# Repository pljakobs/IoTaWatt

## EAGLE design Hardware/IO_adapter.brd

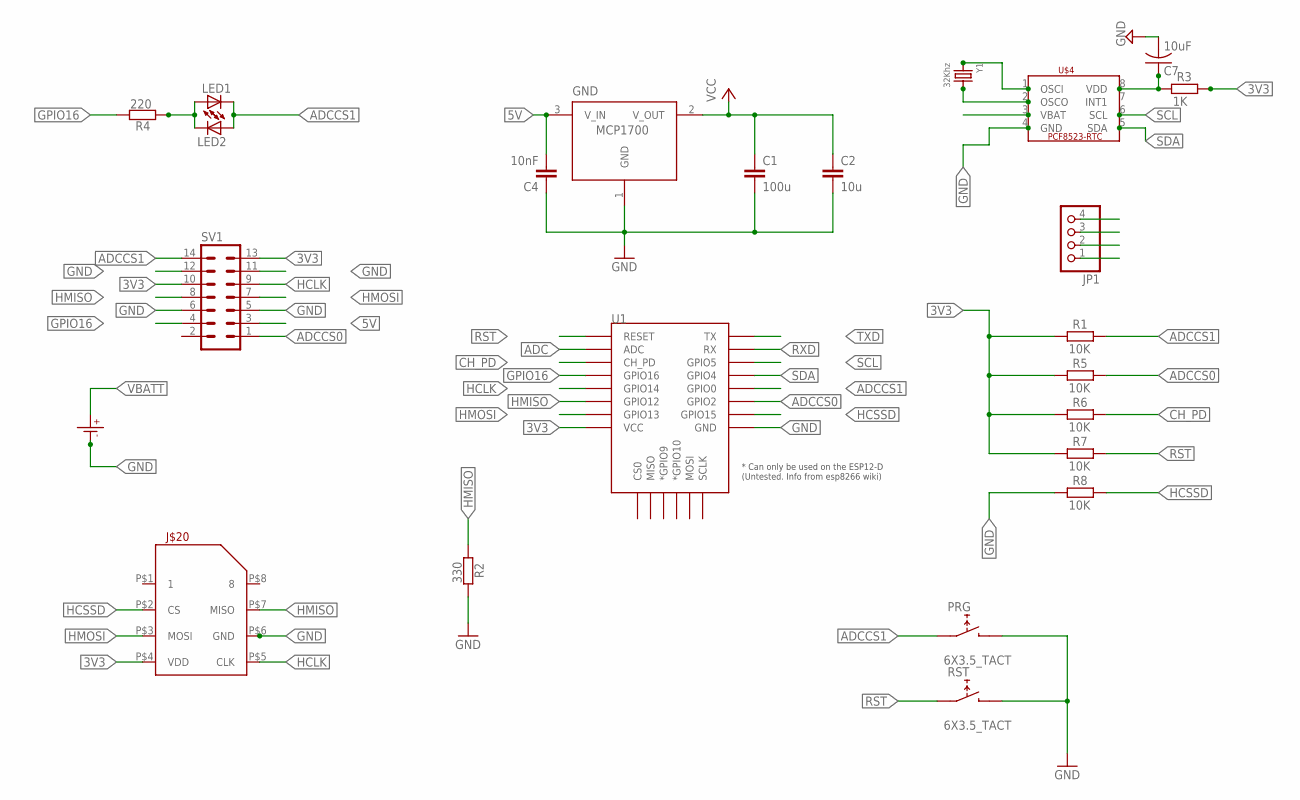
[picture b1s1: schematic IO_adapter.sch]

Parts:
C1: 100u; C0805
C2: 10u; C0805
C4: 10nF; C0805
C7: 10uF; C0805
GND: MCP1700SOT23; SOT-23
J$20: MICROSD_PUSH/PULL; MICROSD
JP1: PINHD-1X4; 1X04
LED1, LED2: LEDCHIPLED_0805; CHIPLED_0805
PRG: 6X3.5_TACT; TACT_6X3.5
R1, R5, R6, R7, R8: 10K; R0805
R2: 330; R0805
R3: 1K; R0805
R4: 220; R0805
RST: 6X3.5_TACT; TACT_6X3.5
SV1: MA07-2
U1: ESP12ESMD; ESP12E-SMD
U$1: CR1220SMD
U$4: PCF8523_RTC; SOIC_8
Y1: 32Khz; CRYSTAL_8X3.8

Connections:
3V3: C1.1, C2.1, GND.2 (V_OUT), J$20.P$4 (VDD), JP1.1, R1.1, R3.2, R5.1, R6.1, R7.1, SV1.10, SV1.13, U1.VCC
5V: C4.2, GND.3 (V_IN), SV1.3
ADC: U1.ADC
ADCCS0: R5.2, SV1.1, U1.GPIO2
ADCCS1: LED1.C, LED2.A, PRG.P$1 (1), R1.2, SV1.14, U1.GPIO0
CH_PD: R6.2, U1.CH_PD
GND: C1.2, C2.2, C4.1, C7.2, GND.1 (GND), J$20.P$6 (GND), JP1.4, PRG.P$2 (2), R2.2, R8.1, RST.P$2 (2), SV1.5, SV1.6, SV1.11, SV1.12, U1.GND, U$1.P- (P$-), U$4.4 (GND)
GPIO16: R4.2, SV1.4, U1.GPIO16
HCLK: J$20.P$5 (CLK), SV1.9, U1.GPIO14
HCSSD: J$20.P$2 (CS), R8.2, U1.GPIO15
HMISO: J$20.P$7 (MISO), R2.1, SV1.8, U1.GPIO12
HMOSI: J$20.P$3 (MOSI), SV1.7, U1.GPIO13
unnamed: C7.1, R3.1, U$4.8 (VDD)
unnamed: LED1.A, LED2.C, R4.1
unnamed: U$4.2 (OSCO), Y1.P$4 (2)
unnamed: U$4.1 (OSCI), Y1.P$1 (1)
RST: R7.2, RST.P$1 (1), U1.RESET
RXD: JP1.2, U1.RXD0 (RX)
SCL: U1.GPIO5, U$4.6 (SCL)
SDA: U1.GPIO4, U$4.5 (SDA)
TXD: JP1.3, U1.TXD0 (TX)
VBATT: U$1.P+ (P$+), U$4.3 (VBAT)

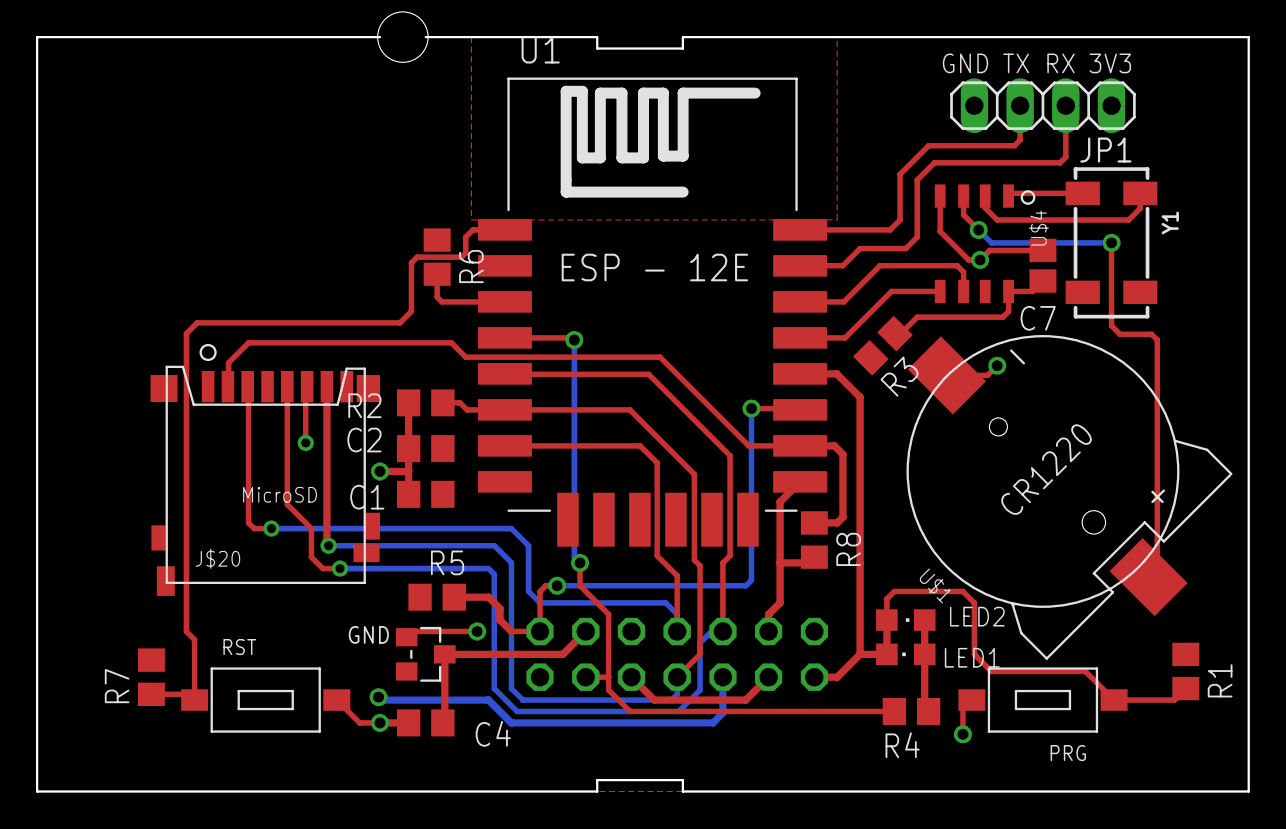
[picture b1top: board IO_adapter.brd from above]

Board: 2 copper layers, 67.3 x 41.9 mm, 24 parts (1 on the bottom side), 21 nets.

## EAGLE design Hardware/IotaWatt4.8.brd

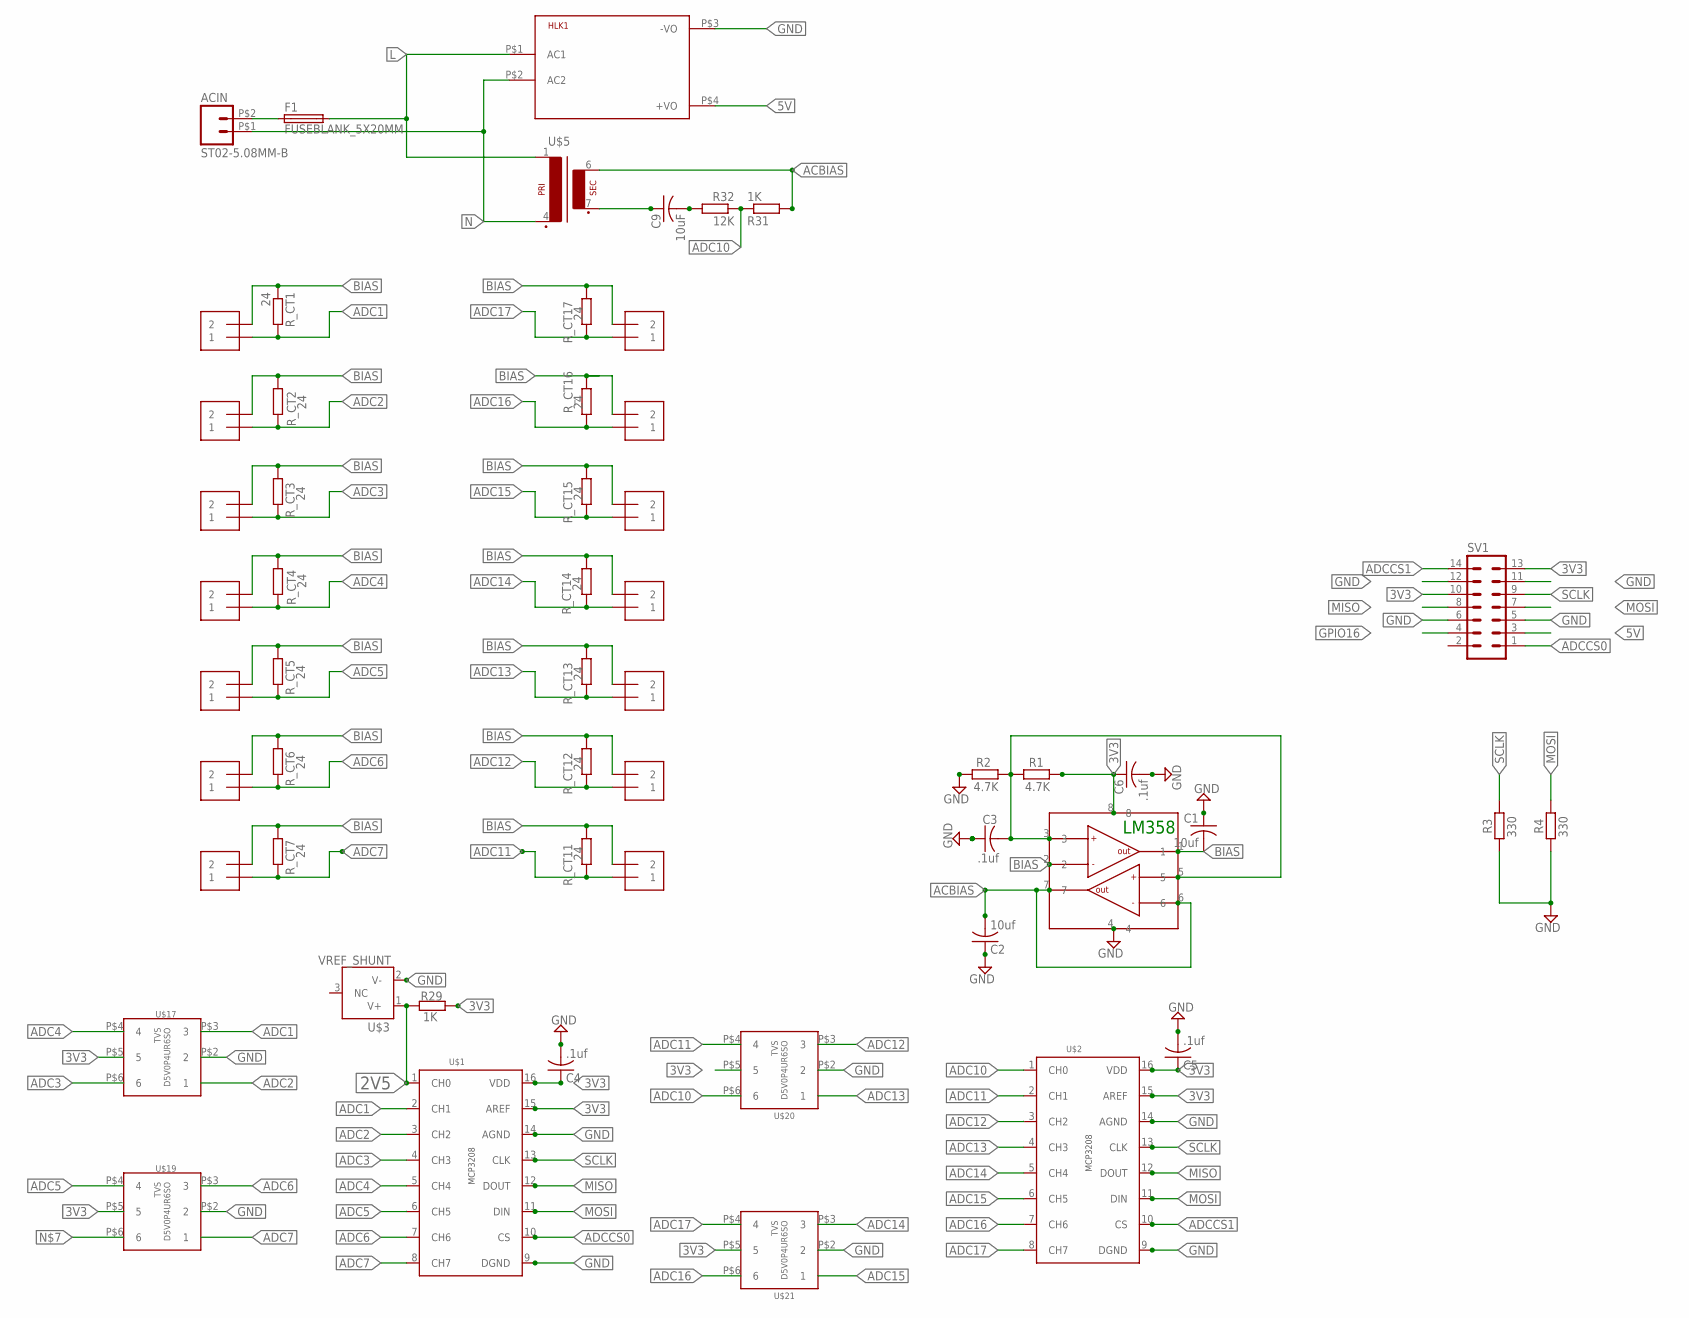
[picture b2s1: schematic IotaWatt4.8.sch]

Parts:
ACIN: ST02-5.08MM-B; EK500V4R-B
C1, C2: 10uf; C0805
C3, C4, C5, C6: .1uf; C0805
C9: 10uF; C0805
CT1, CT2, CT3, CT4, CT5, CT6, CT7, CT11, CT12, CT13, CT14, CT15, CT16, CT17: 1X2-3.5MM; 3.5MMTERM
F1: FUSEBLANK_5X20MM; FUSE_HOLDER_5X20MM
HLK1: HLK-PM013W; HLK-PM01
R1, R2: 4.7K; R0805
R3, R4: 330; R0805
R29, R31: 1K; R0805
R32: 12K; R0805
R_CT1, R_CT2, R_CT3, R_CT4, R_CT5, R_CT6, R_CT7, R_CT11, R_CT12, R_CT13, R_CT14, R_CT15, R_CT16, R_CT17: 24; R0805
SV1: MA07-2
U$1, U$2: MCP3208; SOIC_16
U$3: VREF_SHUNT; SOT23_3
U$5: BV20_1P1S; BV20
U$17, U$19, U$20, U$21: TVS_4CHAN_ARRAYSC-74; SC-74
U$22: LM358_DUAL_OP-AMP; SOIC_8

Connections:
2V5: R29.2, U$1.1 (CH0), U$3.1 (V+)
3V3: C4.1, C5.1, C6.1, R1.2, R29.1, SV1.10, SV1.13, U$1.15 (AREF), U$1.16 (VDD), U$2.15 (AREF), U$2.16 (VDD), U$17.P$5 (5), U$19.P$5 (5), U$20.P$5 (5), U$21.P$5 (5), U$22.8
5V: HLK1.P$4 (+VO), SV1.3
ACBIAS: C2.2, R31.2, U$5.6 (S4), U$22.6, U$22.7
ADC1: CT1.1, R_CT1.2, U$1.2 (CH1), U$17.P$3 (3)
ADC2: CT2.1, R_CT2.2, U$1.3 (CH2), U$17.P$1 (1)
ADC3: CT3.1, R_CT3.2, U$1.4 (CH3), U$17.P$6 (6)
ADC4: CT4.1, R_CT4.2, U$1.5 (CH4), U$17.P$4 (4)
ADC5: CT5.1, R_CT5.2, U$1.6 (CH5), U$19.P$4 (4)
ADC6: CT6.1, R_CT6.2, U$1.7 (CH6), U$19.P$3 (3)
ADC7: CT7.1, R_CT7.2, U$1.8 (CH7), U$19.P$1 (1)
ADC10: R31.1, R32.1, U$2.1 (CH0), U$20.P$6 (6)
ADC11: CT11.1, R_CT11.2, U$2.2 (CH1), U$20.P$4 (4)
ADC12: CT12.1, R_CT12.2, U$2.3 (CH2), U$20.P$3 (3)
ADC13: CT13.1, R_CT13.2, U$2.4 (CH3), U$20.P$1 (1)
ADC14: CT14.1, R_CT14.2, U$2.5 (CH4), U$21.P$3 (3)
ADC15: CT15.1, R_CT15.2, U$2.6 (CH5), U$21.P$1 (1)
ADC16: CT16.1, R_CT16.2, U$2.7 (CH6), U$21.P$6 (6)
ADC17: CT17.1, R_CT17.2, U$2.8 (CH7), U$21.P$4 (4)
ADCCS0: SV1.1, U$1.10 (CS)
ADCCS1: SV1.14, U$2.10 (CS)
BIAS: C1.2, CT1.2, CT2.2, CT3.2, CT4.2, CT5.2, CT6.2, CT7.2, CT11.2, CT12.2, CT13.2, CT14.2, CT15.2, CT16.2, CT17.2, R_CT1.1, R_CT2.1, R_CT3.1, R_CT4.1, R_CT5.1, R_CT6.1, R_CT7.1, R_CT11.1, R_CT12.1, R_CT13.1, R_CT14.1, R_CT15.1, R_CT16.1, R_CT17.1, U$22.1, U$22.2
GND: C1.1, C2.1, C3.1, C4.2, C5.2, C6.2, HLK1.P$3 (-VO), R2.1, R3.1, R4.1, SV1.5, SV1.6, SV1.11, SV1.12, U$1.9 (DGND), U$1.14 (AGND), U$2.9 (DGND), U$2.14 (AGND), U$3.2 (V-), U$17.P$2 (2), U$19.P$2 (2), U$20.P$2 (2), U$21.P$2 (2), U$22.4
GPIO16: SV1.4
L: F1.2, HLK1.P$1 (AC1), U$5.1
MISO: SV1.8, U$1.12 (DOUT), U$2.12 (DOUT)
MOSI: R4.2, SV1.7, U$1.11 (DIN), U$2.11 (DIN)
N: ACIN.P$1 (1), HLK1.P$2 (AC2), U$5.4 (P2)
unnamed: ACIN.P$2 (2), F1.1
unnamed: C9.2, R32.2
unnamed: C9.1, U$5.7 (S3)
SCLK: R3.2, SV1.9, U$1.13 (CLK), U$2.13 (CLK)
VREF: C3.2, R1.1, R2.2, U$22.3, U$22.5

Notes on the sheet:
LM358

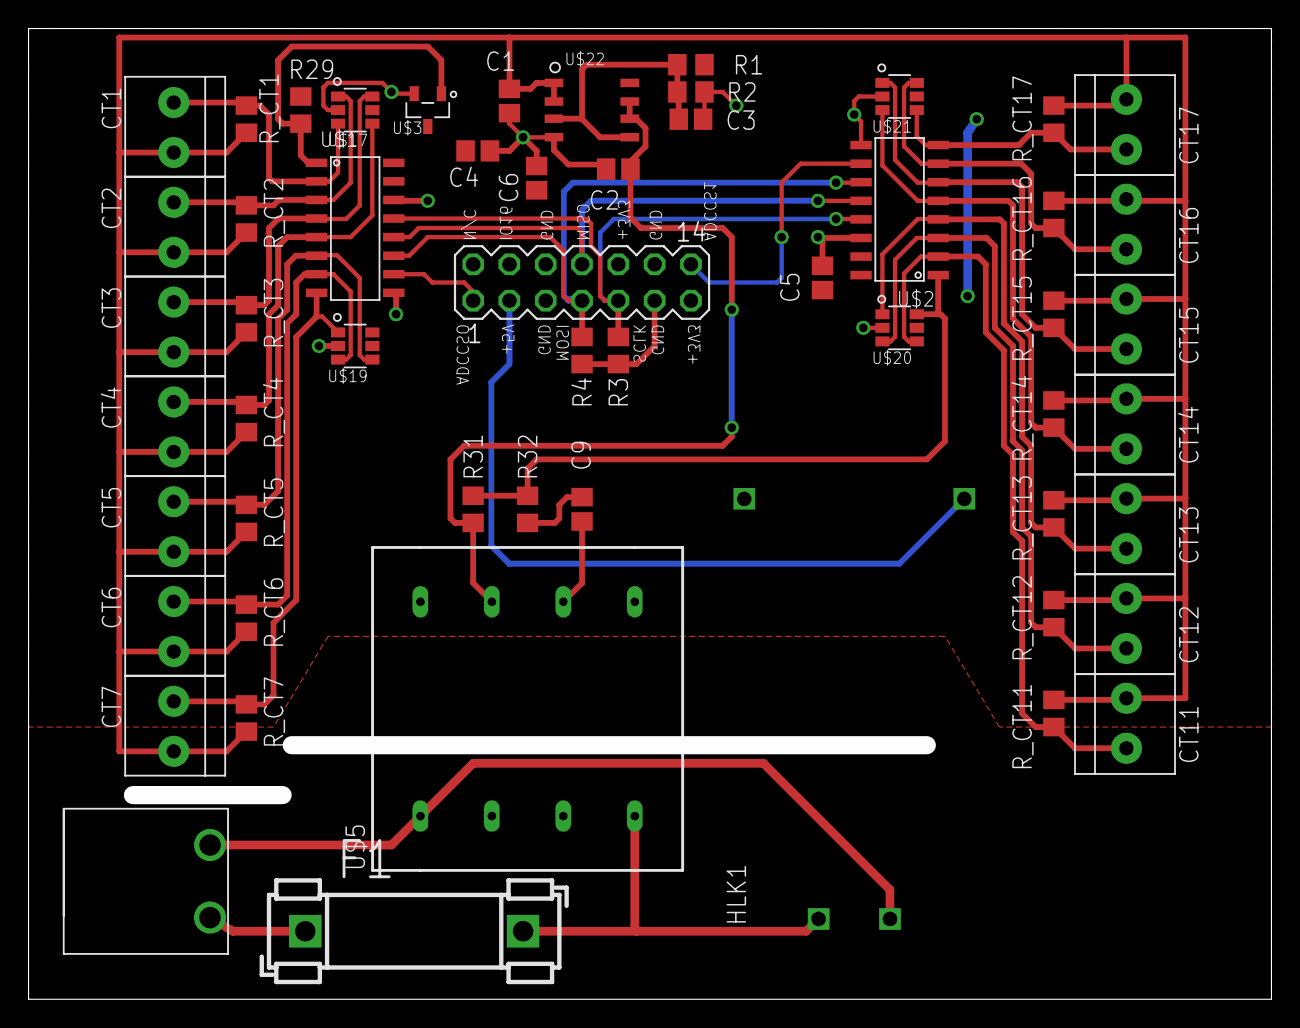
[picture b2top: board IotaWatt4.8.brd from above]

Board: 2 copper layers, 87.0 x 67.9 mm, 55 parts (0 on the bottom side), 32 nets.

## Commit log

2019-11-21 corrected sd card orientation
2019-11-22 corrected a major mistake
    I had connected MOSI/MISO/SCLK to the primary hw SPI - now they are correctly conntected to the secondary bus.
    MOSI->HSPI-D(GPIO13)
    MISO->HSPI-Q(GPIO12)
    SCLK->HSPI-CLK(GPIO14)
    CSSD->HSPI-CD(GPIO15)
    also added some minor changes to better fit the case
2020-03-08 SPI termination resistor positions
    added SPI termination resistor positions
2020-03-08 mechanical fitting
    moved the clamp positions such that they should fit unmodified.
    Added silkscreen signal names for the power board ribbon connector, improved 3V3 connection on IO Board
2020-03-08 minor schematic cleanup
    just moved a few components around on the schematic

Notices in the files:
parts and their libraries:
microbuilder: This work is placed in the public domain, and may be freely used for commercial and non-commercial work with the following conditions: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
